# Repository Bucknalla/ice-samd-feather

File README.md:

View this project on [CADLAB.io](https://cadlab.io/project/2517). 

# ice-samd-feather

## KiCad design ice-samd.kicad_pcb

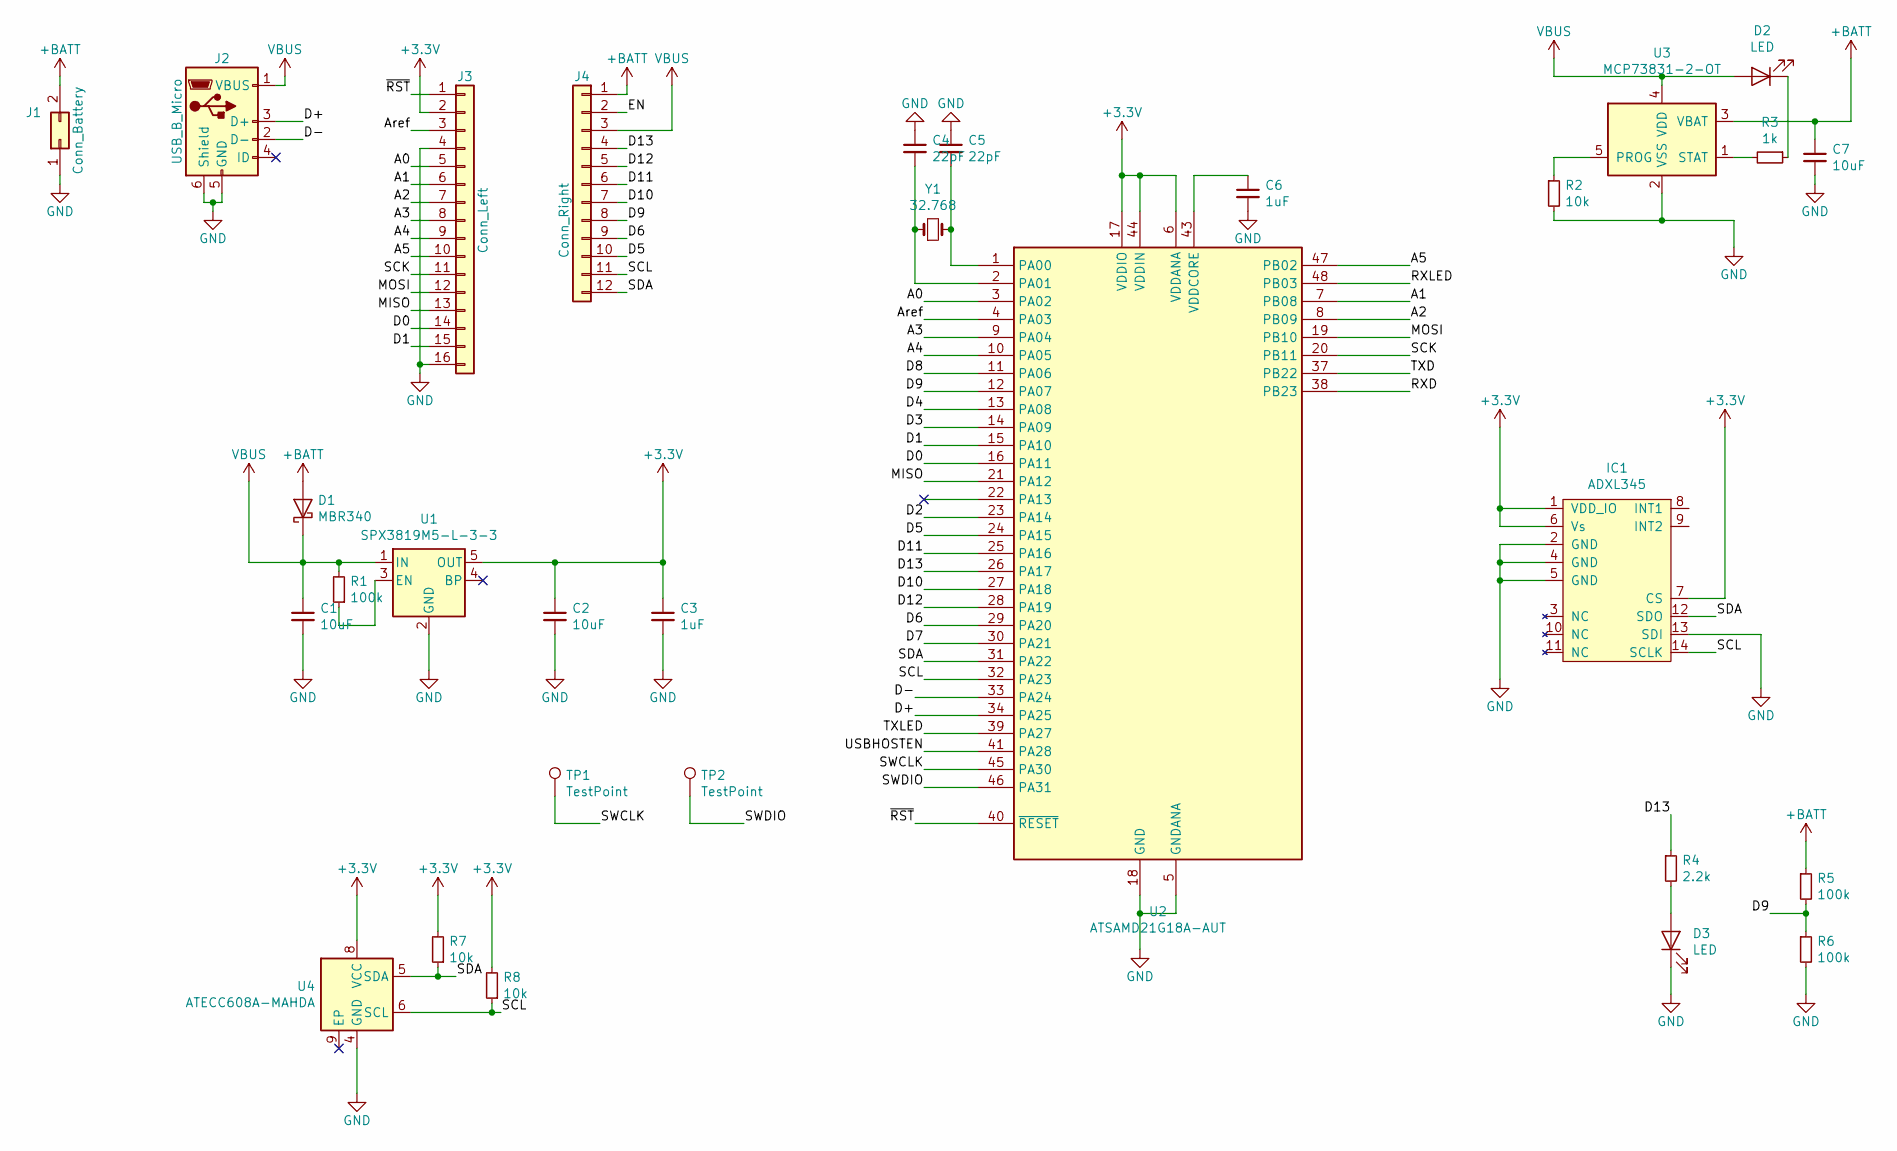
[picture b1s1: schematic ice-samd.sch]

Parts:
C1, C2, C7: 10uF; C_0603_1608Metric
C3, C6: 1uF; C_0603_1608Metric
C4, C5: 22pF; C_0603_1608Metric
D1: MBR340; D_0805_2012Metric
D2, D3: LED; LED_0603_1608Metric
IC1: ADXL345; ADXL3x5; Farnell 1853935
J1: Conn_Battery; JST_PH_B2B-PH-SM4-TB_1x02-1MP_P2.00mm_Vertical
J2: USB_B_Micro; USB_Micro-B_Molex-105017-0001
J3: Conn_Left; PinSocket_1x16_P2.54mm_Vertical
J4: Conn_Right; PinSocket_1x12_P2.54mm_Vertical
R1, R5, R6: 100k; R_0603_1608Metric
R2, R7, R8: 10k; R_0603_1608Metric
R3: 1k; R_0603_1608Metric
R4: 2.2k; R_0603_1608Metric
TP1, TP2: TestPoint; TestPoint_Pad_D1.0mm
U1: SPX3819M5-L-3-3; SOT-23-5
U2: ATSAMD21G18A-AUT; QFN-48-1EP_7x7mm_P0.5mm_EP5.15x5.15mm
U3: MCP73831-2-OT; SOT-23-5
U4: ATECC608A-MAHDA; DFN-8-1EP_3x2mm_P0.5mm_EP1.3x1.5mm
Y1: 32.768; Crystal_SMD_EuroQuartz_EQ161-2Pin_3.2x1.5mm

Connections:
+3V3: C2.1, C3.1, IC1.1 (VDD_IO), IC1.6 (Vs), IC1.7 (CS), J3.2, R7.2, R8.2, U1.5 (OUT), U2.6 (VDDANA), U2.17 (VDDIO), U2.36 (VDDIO), U2.44 (VDDIN), U4.8 (VCC)
+BATT: C7.1, D1.2 (A), J1.2, J4.1, R5.1, U3.3 (VBAT)
/A0: J3.5, U2.3 (PA02)
/A1: J3.6, U2.7 (PB08)
/A2: J3.7, U2.8 (PB09)
/A3: J3.8, U2.9 (PA04)
/A4: J3.9, U2.10 (PA05)
/A5: J3.10, U2.47 (PB02)
/Aref: J3.3, U2.4 (PA03)
/D0: J3.14, U2.16 (PA11)
/D1: J3.15, U2.15 (PA10)
/D2: U2.23 (PA14)
/D3: U2.14 (PA09)
/D4: U2.13 (PA08)
/D5: J4.10, U2.24 (PA15)
/D6: J4.9, U2.29 (PA20)
/D7: U2.30 (PA21)
/D8: U2.11 (PA06)
/D9: J4.8, R5.2, R6.1, U2.12 (PA07)
/D10: J4.7, U2.27 (PA18)
/D11: J4.6, U2.25 (PA16)
/D12: J4.5, U2.28 (PA19)
/D13: J4.4, R4.1, U2.26 (PA17)
/D+: J2.3 (D+), U2.34 (PA25)
/D-: J2.2 (D-), U2.33 (PA24)
/EN: J4.2
/MISO: J3.13, U2.21 (PA12)
/MOSI: J3.12, U2.19 (PB10)
/RXD: U2.38 (PB23)
/RXLED: U2.48 (PB03)
/SCK: J3.11, U2.20 (PB11)
/SCL: IC1.14 (SCLK), J4.11, R8.1, U2.32 (PA23), U4.6 (SCL)
/SDA: IC1.12 (SDO), J4.12, R7.1, U2.31 (PA22), U4.5 (SDA)
/SWCLK: TP1.1, U2.45 (PA30)
/SWDIO: TP2.1, U2.46 (PA31)
/TXD: U2.37 (PB22)
/TXLED: U2.39 (PA27)
/USBHOSTEN: U2.41 (PA28)
/~RST~: J3.1, U2.40 (~RESET)
GND: C1.2, C2.2, C3.2, C4.1, C5.1, C6.2, C7.2, D3.1 (K), IC1.2 (GND), IC1.4 (GND), IC1.5 (GND), IC1.13 (SDI), J1.1, J2.5 (GND), J2.6 (Shield), J3.4, J3.16, R2.2, R6.2, U1.2 (GND), U2.5 (GNDANA), U2.18 (GND), U2.35 (GND), U2.42 (GND), U2.49, U3.2 (VSS), U4.4 (GND)
unnamed: C4.2, U2.2 (PA01), Y1.1
unnamed: C5.2, U2.1 (PA00), Y1.2
unnamed: C6.1, U2.43 (VDDCORE)
unnamed: D2.1 (K), R3.1
unnamed: D3.2 (A), R4.2
unnamed: R1.1, U1.3 (EN)
unnamed: R2.1, U3.5 (PROG)
unnamed: R3.2, U3.1 (STAT)
VBUS: C1.1, D1.1 (K), D2.2 (A), J2.1 (VBUS), J4.3, R1.2, U1.1 (IN), U3.4 (VDD)

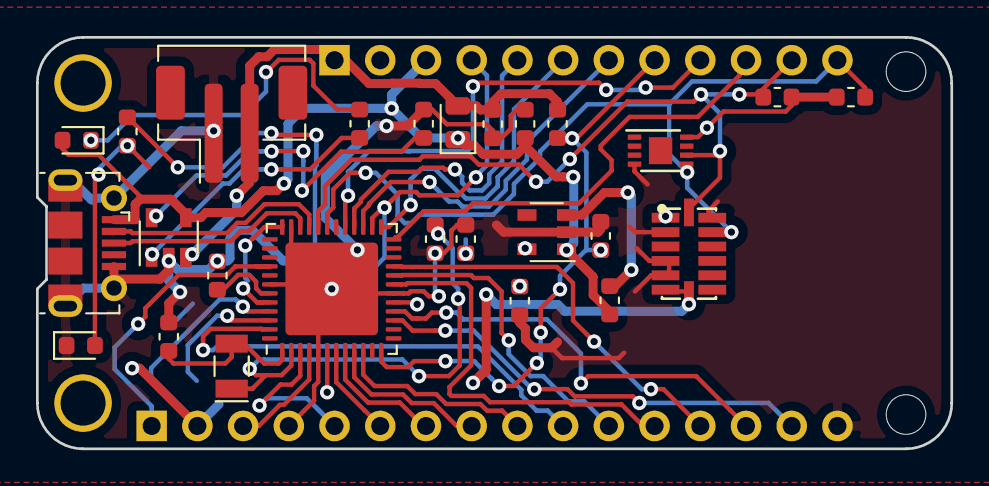
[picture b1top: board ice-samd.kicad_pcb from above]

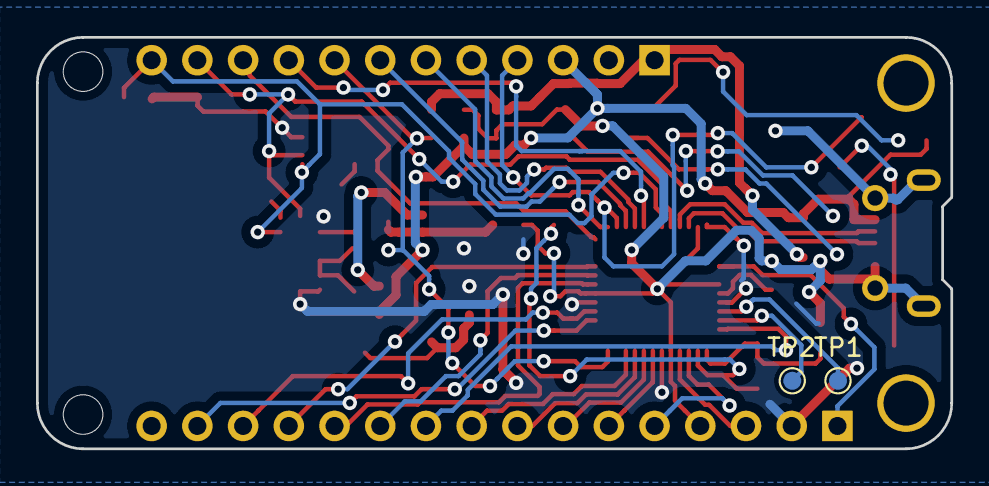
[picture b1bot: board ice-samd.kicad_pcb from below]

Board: 2 copper layers, 50.8 x 22.9 mm, 30 parts (2 on the bottom side), 38 nets.

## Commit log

2019-12-11 Added gitignore
2019-12-11 WIP initial commit
2020-01-18 Updated samd21
2020-02-22 Backlink to CADLAB.io has been added.
2020-02-26 Updated LED locations
2020-02-26 cleaned up traces
